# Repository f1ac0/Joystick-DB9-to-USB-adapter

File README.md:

# Joystick DB9 to USB adapter
Connect an Atari/Amiga joystick or mouse to your PC using USB.

While plugging or powering up the adapter :
- leave all buttons disconnected to use a standard 1-3 buttons joystick or a CD32 pad (not really tested)
- press button 1 to control the PC mouse pointer using the joystick
- press button 2/right mouse button to use an Amiga mouse to control the PC pointer
- press both button 1 and 2/left and right mouse buttons to use an Atari mouse to control the PC pointer

# Disclaimer
This is a hobbyist project, it comes with no warranty and no support.

I publish my work under the CC-BY-NC-SA license.

If you find it useful and want to reward my hard work : I am always looking for Amiga/Atari/Amstrad/Commodore/Sinclair/Thomson... hardware to repair and hack, please contact me.

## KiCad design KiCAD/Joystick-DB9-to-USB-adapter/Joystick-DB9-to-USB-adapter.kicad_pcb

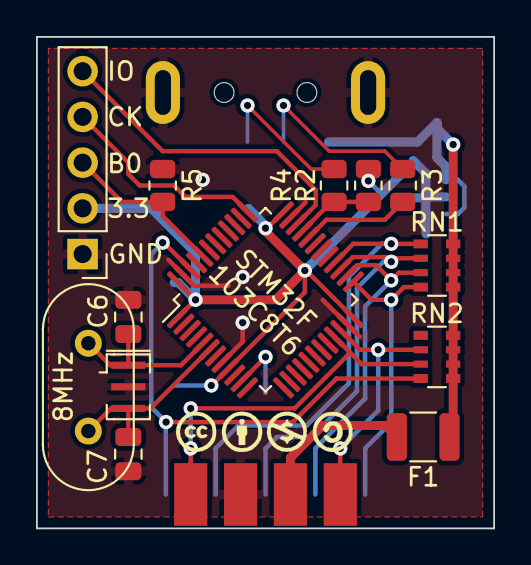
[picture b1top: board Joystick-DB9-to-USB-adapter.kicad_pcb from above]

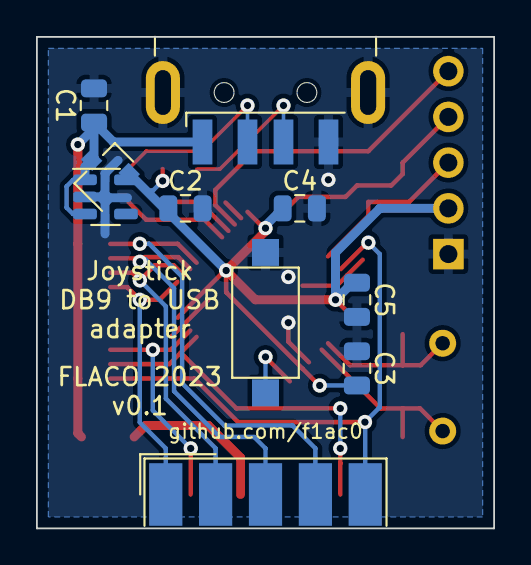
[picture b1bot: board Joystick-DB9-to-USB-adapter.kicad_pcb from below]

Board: 2 copper layers, 25.4 x 27.3 mm, 24 parts (10 on the bottom side), 21 nets.

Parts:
C1, C2: 1u; C_0805_2012Metric
C3, C4, C5: 100n; C_0805_2012Metric
C6, C7: 22p; C_0805_2012Metric
F1: Polyfuse 0.5A max; R_1210_3225Metric
FID1: License; CC_BY_NC_SA_long_silkscreen_11.4x3.5
J1: DE9_Receptacle; DSUB-9_Male_EdgeMount_P2.77mm
J2: USB_A; USB_A_CNCTech_1001-011-01101_Horizontal
J3: Prog; PinHeader_1x05_P2.54mm_Vertical
R2: 10k; R_0805_2012Metric
R3, R4: 22; R_0805_2012Metric
R5: 100k; R_0805_2012Metric
RN1, RN2: 10k; R_Array_Convex_4x0603
SW1: SEL; SW_SPST_CK_RS282G05A3
U1: STM32F103C8Tx; LQFP-48_7x7mm_P0.5mm
U2: SPX3819M5-L-3-3; SOT-23-5
U3: XC6206PxxxMR; SOT-23
Y1: 8.000; Crystal_HC49-4H_Vertical
Y2: 8MHz; Resonator_SMD_Murata_CSTxExxV-3Pin_3.0x1.1mm

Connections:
5V: F1.1, J1.7
+3.3V: C2.1, C3.1, C4.1, C5.1, J3.2, R2.1, U1.1 (VBAT), U1.9 (VDDA), U1.24 (VDD), U1.36 (VDD), U1.48 (VDD), U2.5 (OUT), U3.2 (VO)
+5V: C1.1, F1.2, J2.1 (VBUS), RN1.5 (R4.2), RN1.6 (R3.2), RN1.7 (R2.2), RN1.8 (R1.2), RN2.5 (R4.2), RN2.6 (R3.2), RN2.7 (R2.2), RN2.8 (R1.2), U2.1 (IN), U2.3 (EN), U3.3 (VI)
/BOOT0: J3.3, R5.1, U1.44 (BOOT0)
/SWCLK: J3.4, U1.37 (PA14)
/SWDIO: J3.5, U1.34 (PA13)
/USB_D+: J2.3 (D+), R4.1
/USB_D-: J2.2 (D-), R3.1
GND: C1.2, C2.2, C3.2, C4.2, C5.2, C6.2, C7.2, J1.8, J2.4 (GND), J2.5 (Shield), J3.1, R5.2, SW1.2, U1.8 (VSSA), U1.23 (VSS), U1.35 (VSS), U1.47 (VSS), U2.2 (GND), U3.1 (GND), Y2.2
J: SW1.1, U1.11 (PA1)
unnamed: R3.2, U1.32 (PA11)
unnamed: R2.2, R4.2, U1.33 (PA12)
unnamed: C6.1, U1.5 (PD0), Y1.1, Y2.1
unnamed: C7.1, U1.6 (PD1), Y1.2, Y2.3
/DOWN: J1.2, RN1.3 (R3.1), U1.26 (PB13)
/F1_CLK: J1.6, RN2.2 (R2.1), U1.22 (PB11)
/F2_DATA: J1.9, RN2.3 (R3.1), U1.21 (PB10)
/F3_LOAD_SHIFT: J1.5, RN2.4 (R4.1), U1.46 (PB9)
/LEFT: J1.3, RN1.2 (R2.1), U1.27 (PB14)
/RIGHT: J1.4, RN1.1 (R1.1), U1.28 (PB15)
/UP: J1.1, RN1.4 (R4.1), U1.25 (PB12)

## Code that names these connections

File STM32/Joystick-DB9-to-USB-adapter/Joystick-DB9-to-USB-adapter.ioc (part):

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Mcu.Name=STM32F103C(8-B)Tx
Mcu.Package=LQFP48
Mcu.UserName=STM32F103C8Tx
PA1.GPIOParameters=GPIO_PuPd,GPIO_Label
PA1.GPIO_Label=BUTTON
PA1.GPIO_PuPd=GPIO_PULLUP
PA1.Signal=GPIO_Input
PA11.Mode=Device
PA11.Signal=USB_DM
PA12.Mode=Device
PA12.Signal=USB_DP
PA13.Mode=Serial_Wire
PA13.Signal=SYS_JTMS-SWDIO
PA14.Mode=Serial_Wire
PA14.Signal=SYS_JTCK-SWCLK
PB10.GPIOParameters=GPIO_Label
PB10.GPIO_Label=F2_DATA
PB10.Signal=GPIO_Input
PB11.GPIOParameters=GPIO_Label
PB11.GPIO_Label=F1_CLK
PB11.Signal=GPIO_Input
PB12.GPIOParameters=GPIO_Label
PB12.GPIO_Label=UP
PB12.Signal=GPIO_Input
PB13.GPIOParameters=GPIO_Label
PB13.GPIO_Label=DOWN
PB13.Signal=GPIO_Input
PB14.GPIOParameters=GPIO_Label
PB14.GPIO_Label=LEFT
PB14.Signal=GPIO_Input
PB15.GPIOParameters=GPIO_Label
PB15.GPIO_Label=RIGHT
PB15.Signal=GPIO_Input
PB9.GPIOParameters=GPIO_Label
PB9.GPIO_Label=F3_LOAD_SHIFT
PB9.Signal=GPIO_Input
PD0-OSC_IN.Mode=HSE-External-Oscillator
PD0-OSC_IN.Signal=RCC_OSC_IN
PD1-OSC_OUT.Mode=HSE-External-Oscillator
PD1-OSC_OUT.Signal=RCC_OSC_OUT
RCC.SYSCLKFreq_VALUE=72000000
RCC.SYSCLKSource=RCC_SYSCLKSOURCE_PLLCLK
board=custom

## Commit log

2024-03-13 Repository init with KiCad files, STM32 code, Readme and License

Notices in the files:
KiCAD/Joystick-DB9-to-USB-adapter/Joystick-DB9-to-USB-adapter.kicad_pcb:
FLACO 2023 CC-BY-NC-SA
